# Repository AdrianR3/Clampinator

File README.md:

# The Clampinator

Inspired by the [ODrive Regen Clamp](https://shop.odriverobotics.com/products/odrive-regeneration-clamp), the clampinator is a custom built regeneration clamp targeting 16-60V systems.

## Key Features
 - 16-60V input
 - Adjustable clamp voltage via trimpot
 - Full reverse current protection via TI's [LM7481-Q1](https://www.ti.com/product/LM7481-Q1)
   - Ideal diode inrush current limiting supported, but marked as DNP
 - External pre-charge resistor
 - **FULL galvanic isolation between power and logic domains**
 - USB-C port for programming
 - STM32H5 based logic control
   - Digital control to disconnect power input from output
   - 2x CAN FD exposed w/toggleable termination resistors
 - Two onboard LEDs (Yellow and RGB)
 - Two 10k thermistor slots for thermistors
 - Two 15V outputs for active cooling fans

> [!CAUTION]
> The Clampinator must not be plugged in unless the power switch is off. To turn on, slide power switch to `PRECHARGE`, and only proceed to `RUN` after allowing at least 1s for the bulk capacitors to charge.

## Using the CAN bus

The STM32 on the board is equipped with two built in CAN FD controllers, and the Clampinator has two accompanying CAN transcievers in the bottom left of the board. There is dip switch `SW5` which can be used to toggle the internal 120Ω termination resistors.

## Building the Clampinator
The Clampinator can be ordered from sites like JLCPCB. The KiCAD source files are in `./KiCAD` and the production gerber files are in `./KiCAD/prod` along with the bom.

## Images 

## Schematic

### Main Circuit

## Logic Side Circuit

## Thermal Management

## BOM

| **Name**              | **Purpose**                                     | **Quantity** | **Total Cost (USD)** | **Link**                                                                                                                      | **Distributor**   |
|-----------------------|-------------------------------------------------|--------------|----------------------|-------------------------------------------------------------------------------------------------------------------------------|-------------------|
| LCSC Parts            | Majority of PCB Components (With GSDL selected) |              | 124.28               |                                                                                                                               | LCSC              |
| 150R 25W Resistor     | Precharge Resistor (Inrush Current Limiting)    | 1            | 5.19                 | https://www.digikey.com/en/products/detail/riedon-products-by-bourns/UAL25-150RF8/3886469                                     | DigiKey           |
| 1818-VP036584000AG-ND | Connect Main Power                              | 2            | 5.50                 | https://www.digikey.com/en/products/detail/amphenol-anytek/VP036584000AG/10378245                                             | DigiKey           |
| 1818-VP0265840000G-ND | Connect Precharge Resistor                      | 1            | 3.10                 | https://www.digikey.com/en/products/detail/amphenol-anytek/VP0265840000G/10378270                                             | DigiKey           |
| EG1847-ND             | Switch for Logic Side of Board                  |              | 0.89                 | https://www.digikey.com/en/products/detail/e-switch/EG1270/6076                                                               | DigiKey           |
| 259-1805-ND           | Active Cooling Fan (price includes est. tariff) | 2            | 15.48                | https://www.digikey.com/en/products/detail/sunon-fans/MF80252V1-1000U-A99/6198743                                             | DigiKey           |
| SW115-ND              | (GPI-154-3013) Precharge Switch                 |              | 1.83                 | https://www.digikey.com/en/products/detail/cw-industries/GPI-154-3013/902                                                     | DigiKey           |
| 1.6R 500W Resistor    | Main brake resistor                             |              | 29.99                | https://www.youdaelectronics.com/products/1pc-500w-watt-16-ohm-500w-16r-aluminum-housing-wire-wound-resistor-29x52x250mm-3199 | Youda Electronics |
| JLCPCB + Stencil      | Main Clampinator Board                          | 1            | 101.38               |                                                                                                                               | JLCPCB            |

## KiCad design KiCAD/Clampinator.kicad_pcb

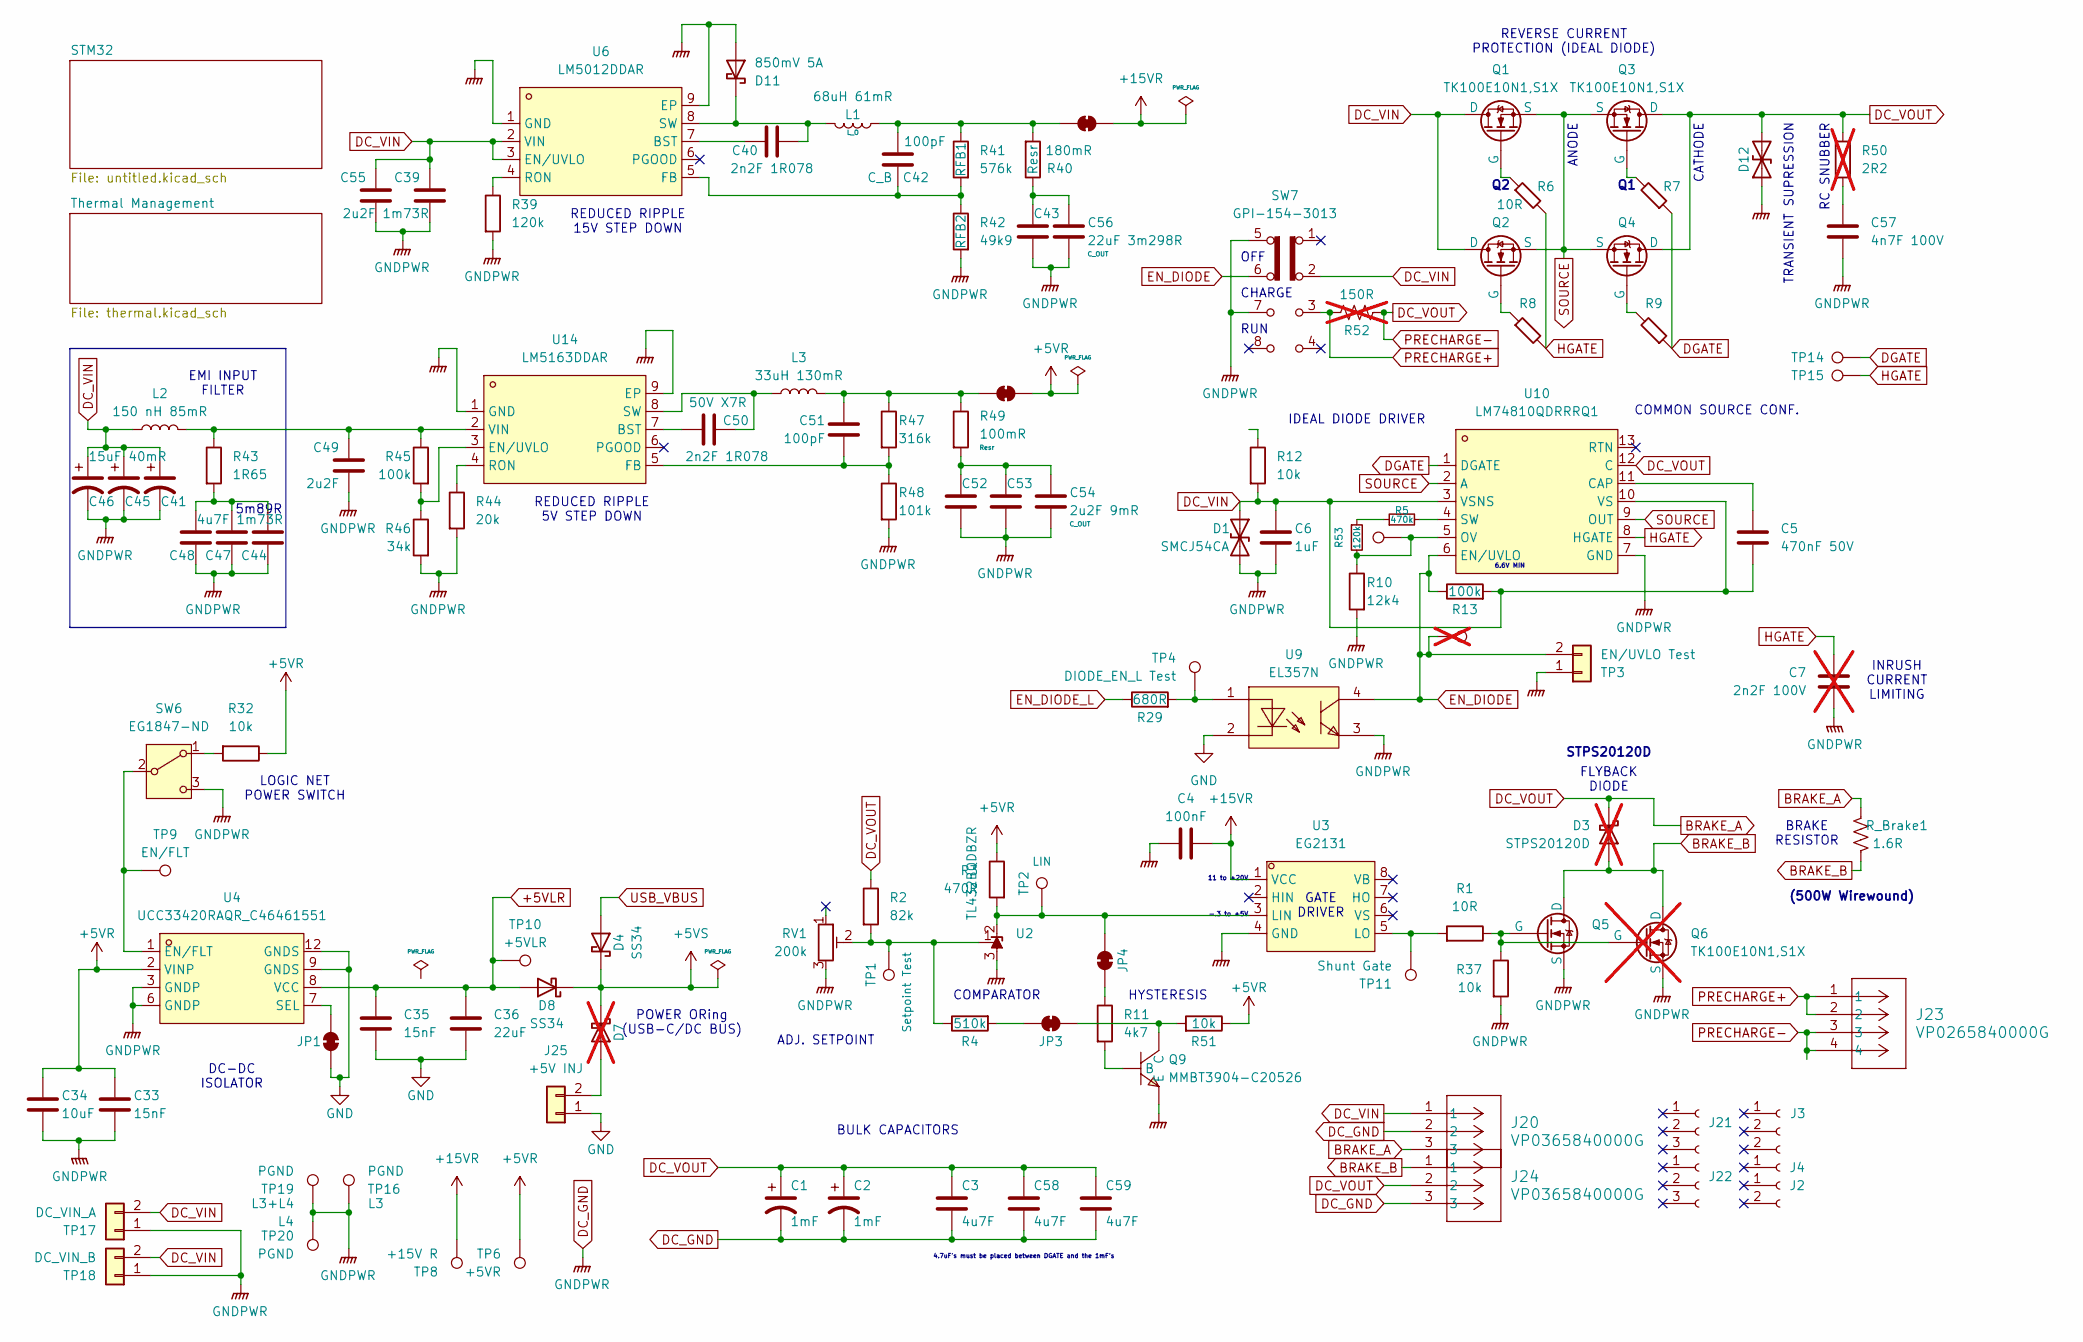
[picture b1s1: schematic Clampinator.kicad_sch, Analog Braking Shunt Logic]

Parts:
C1, C2: 1mF; CP_Radial_D18.0mm_P7.50mm; MPN ECA2AM102; LCSC Part C178408
C3, C58, C59: 4u7F; C_1210_3225Metric; LCSC Part C915836
C4: 100nF; C_0402_1005Metric; LCSC Part C307331
C5: 470nF 50V; C_0603_1608Metric; LCSC Part C1620
C6: 1uF; C_1206_3216Metric; LCSC Part C13832
C7: 2n2F 100V; C_0603_1608Metric; not fitted
C33, C35: 15nF; C_0402_1005Metric; LCSC Part C1548
C34: 10uF; C_0805_2012Metric; LCSC Part C15850
C36: 22uF; C_1206_3216Metric; LCSC Part C12891
C39, C55: 2u2F 1m73R; C_1206_3216Metric; LCSC Part C5122251
C40, C50: 2n2F 1R078; C_0603_1608Metric; LCSC Part C1604
C41, C45, C46: 15uF 40mR; CAP-SMD_BD8.0-L8.3-W8.3-LS9.3-FD; MPN 100SXV15M; LCSC Part C542593
C42, C51: 100pF; C_0402_1005Metric; LCSC Part C1546
C43, C56: 22uF 3m298R; C_1206_3216Metric; LCSC Part C12891
C44, C47, C48: 4u7F 1m73R; C_1210_3225Metric; LCSC Part C915836
C49: 2u2F; C_1206_3216Metric; LCSC Part C5122251
C52, C53, C54: 2u2F 9mR; C_1206_3216Metric; LCSC Part C5122251
C57: 4n7F 100V; C_1206_3216Metric; LCSC Part C393168
D1: SMCJ54CA; SMC_L6.9-W5.9-LS7.9-BI; MPN SMCJ54CA-13-F; LCSC Part C135179
D3: STPS20120D; TO-220AC_L10.0-W4.5-P5.08-T; MPN STPS20120D; LCSC Part C10623; not fitted
D4, D8: SS34; D_SMA; LCSC Part C8678
D7: SS34; D_SMA; LCSC Part C8678; not fitted
D11: 850mV 5A; D_SMA; LCSC Part C65010
D12: SMCJ64CA; SMC_L6.9-W5.9-LS7.9-BI; MPN SMCJ64CA/TR13; LCSC Part C123977
J2, J3, J4: Conn_01x02_Socket; PinHeader_1x02_P2.54mm_Vertical
J20, J24: VP0365840000G; VP0265840000G_THT; DigiKey BOM YES
J21, J22: Conn_01x03_Socket
J23: VP0265840000G; CONN04_VP026584_20P32X18P3_AMP; DigiKey BOM YES
J25: +5V INJ; PinHeader_1x02_P2.54mm_Vertical
JP1: SolderJumper_2_Bridged; SolderJumper-2_P1.3mm_Bridged2Bar_RoundedPad1.0x1.5mm
JP3, JP4: SolderJumper_2_Bridged; SolderJumper-2_P1.3mm_Bridged_RoundedPad1.0x1.5mm
JP5: SolderJumper_2_Bridged; SolderJumper-2_P1.3mm_Bridged2Bar_Pad1.0x1.5mm
JP6: +15VR; SolderJumper-2_P1.3mm_Bridged2Bar_Pad1.0x1.5mm
L1: 68uH 61mR; IND-SMD_L12.5-W12.5; MPN CYH125-68UH; LCSC Part C7431083
L2: 150 nH 85mR; WE-MAPI_2010; MPN 744383430033; LCSC Part C6069597
L3: 33uH 130mR; IND_SRR6038-330Y; MPN SRR6038-330Y; LCSC Part C2041395
Q1, Q2, Q3, Q4, Q5: TK100E10N1,S1X; TO-220-3_L10.0-W4.5-P2.54-L; MPN TK100E10N1,S1X; LCSC Part C5986394
Q6: TK100E10N1,S1X; TO-220-3_L10.0-W4.5-P2.54-L; MPN TK100E10N1,S1X; LCSC Part C5986394; not fitted
Q9: MMBT3904-C20526; SOT-23-3_L2.9-W1.3-P1.90-LS2.4-BR; MPN MMBT3904(RANGE:100-300); LCSC Part C20526
R1, R6, R7, R8, R9: 10R; R_0805_2012Metric; LCSC Part C17415
R2: 82k; R_0805_2012Metric; LCSC Part C2849357
R3: 470R; R_0603_1608Metric; LCSC Part C23179
R4: 510k; R_0603_1608Metric; LCSC Part C23192
R5: 470k; R_0805_2012Metric; LCSC Part C17709
R10: 12k4; R_0402_1005Metric; LCSC Part C25752
R11: 4k7; R_0402_1005Metric; LCSC Part C25900
R12: 10k; R_1206_3216Metric; LCSC Part C17902
R13, R45: 100k; R_1206_3216Metric; LCSC Part C17900
R29: 680R; R_0603_1608Metric; LCSC Part C23228
R32, R51: 10k; R_0402_1005Metric; LCSC Part C25744
R37: 10k; R_0805_2012Metric; LCSC Part C17414
R39, R53: 120k; R_0603_1608Metric; LCSC Part C25808
R40: 180mR; R_1206_3216Metric; LCSC Part C24436
R41: 576k; R_0603_1608Metric; LCSC Part C245981
R42: 49k9; R_0603_1608Metric; LCSC Part C23184
R43: 1R65; R_1206_3216Metric; LCSC Part C79297
R44: 20k; R_0603_1608Metric; LCSC Part C4184
R46: 34k; R_0805_2012Metric; LCSC Part C2077219
R47: 316k; R_0603_1608Metric; LCSC Part C185340
R48: 101k; R_0805_2012Metric; LCSC Part C7302896
R49: 100mR; R_1206_3216Metric; LCSC Part C25334
R50: 2R2; R_1210_3225Metric; MPN ERJ-P08J2R2V; not fitted
R52: 150R; SolderWire-4sqmm_1x02_P12mm_D3mm_OD6mm; MPN UAL25-150RF8; DigiKey BOM YES; not fitted
RV1: 200k; RES-ADJ-TH_3P-L9.5-W4.9-P2.50-L_3296W; MPN 3296W-1-204LF; LCSC Part C49190460
R_Brake1: 1.6R
SW6: EG1847-ND; SW_EG1270; DigiKey BOM YES
SW7: GPI-154-3013; SW_Slide_GPL-154-3013_DP3T_Angled; DigiKey BOM YES
TP1: Setpoint Test; TestPoint_THTPad_D2.0mm_Drill1.0mm
TP2: LIN; PinHeader_1x01_P2.54mm_Vertical
TP3: EN/UVLO Test; PinHeader_1x02_P2.54mm_Vertical
TP4: DIODE_EN_L Test; TestPoint_THTPad_D2.0mm_Drill1.0mm
TP6: +5VR; TestPoint_THTPad_D2.0mm_Drill1.0mm
TP8: +15V R; TestPoint_THTPad_D2.0mm_Drill1.0mm
TP9: EN/FLT; TestPoint_THTPad_D1.0mm_Drill0.5mm
TP10: +5VLR; TestPoint_THTPad_D1.0mm_Drill0.5mm
TP11: Shunt Gate; PinHeader_1x01_P2.54mm_Vertical
TP13: TestPoint; TestPoint_THTPad_D1.5mm_Drill0.7mm
TP14: D; TestPoint_THTPad_D1.0mm_Drill0.5mm
TP15: H; TestPoint_THTPad_D1.0mm_Drill0.5mm
TP16, TP19, TP20: PGND; TestPoint_THTPad_D2.0mm_Drill1.0mm
TP17: DC_VIN_A; PinHeader_1x02_P2.54mm_Vertical
TP18: DC_VIN_B; PinHeader_1x02_P2.54mm_Vertical
TP-not3: EN/UVLO Test; TestPoint_THTPad_D2.0mm_Drill1.0mm; not fitted
U2: TL432BQDBZR; SOT-23; LCSC Part C53724
U3: EG2131; SOIC-8_L5.0-W4.0-P1.27-LS6.0-BL; MPN EG2131; LCSC Part C193777
U4: UCC33420RAQR_C46461551; VSON-12_L5.0-W4.0-P0.65-TL_PUCC33420QRAQRQ1; MPN UCC33420RAQR; LCSC Part C46461551
U6: LM5012DDAR; SOPOWERPAD-8_L4.9-W3.9-P1.27-LS6.0-BL-EP; MPN LM5012DDAR; LCSC Part C6079494
U9: EL357N; OPTO-SMD-4_L4.4-W4.1-P2.54-LS7.0-TL; MPN EL357N(A)(TA)-G; LCSC Part C42385000
U10: LM74810QDRRRQ1; WSON-12_L3.0-W3.0-P0.50-TL-EP-2; MPN LM74810QDRRRQ1; LCSC Part C3215601
U14: LM5163DDAR; ESOP-8_L4.9-W3.9-P1.27-LS6.0-BL-EP2.6; MPN LM5163DDAR; LCSC Part C2873264

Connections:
+5VLR: C35.1, C36.1, D8.2 (A), TP10.1 (1_1), U4.8 (VCC)
+5VR: C33.1, C34.1, JP5.2 (B), R3.1, R32.1, R51.1, TP6.1 (1_1), U4.2 (VINP); also elsewhere on the board
+5VS: D4.1 (K), D7.1 (K), D8.1 (K); also elsewhere on the board
+15VR: C4.2, JP6.2 (B), TP8.1 (1_1), U3.1 (VCC); also elsewhere on the board
BRAKE_A: C1.1, C2.1, C3.1, C58.1, C59.1, D3.1 (K), D12.2 (A2), J20.3, J23.3, J23.4, J24.2, Q3.1 (D), Q4.1 (D), R2.1, R50.1, R52.2, R_Brake1.2, U10.12 (C)
BRAKE_B: D3.2 (A), J24.1, Q5.1 (D), Q6.1 (D), R_Brake1.1
DC_GND: C1.2, C2.2, C3.2, C4.1, C6.2, C7.2, C33.2, C34.2, C39.2, C41.2, C43.2, C44.2, C45.2, C46.2, C47.2, C48.2, C49.2, C52.2, C53.2, C54.2, C55.2, C56.2, C57.2, C58.2, C59.2, D1.2 (A2), D11.2 (A), D12.1 (A1), J20.2, J24.3, Q5.3 (S), Q6.3 (S), Q9.2 (E), R10.2, R37.2, R39.2, R42.2, R44.2, R46.2, R48.2, RV1.3, SW6.3 (C), SW7.5 (B), SW7.7 (C), TP3.1, TP16.1 (1_1), TP17.1, TP18.1, TP19.1 (1_1), TP20.1 (1_1), U2.3 (A), U3.4 (GND), U4.3 (GNDP), U4.6 (GNDP), U6.1 (GND), U6.9 (EP), U9.3 (EM), U10.7 (GND), U14.1 (GND), U14.9 (EP); also elsewhere on the board
DC_VIN: C5.2, C6.1, C39.1, C41.1, C45.1, C46.1, C55.1, D1.1 (A1), J20.1, L2.1, Q1.1 (D), Q2.1 (D), R12.2, R13.2, SW7.2 (B), TP17.2, TP18.2, U6.2 (VIN), U6.3 (EN/UVLO), U10.3 (VSNS), U10.10 (VS)
DGATE: R7.1, R9.1, TP14.1 (1_1), U10.1 (DGATE)
EN_DIODE: R13.1, SW7.6 (C), TP3.2, TP-not3.1, U9.4 (COL), U10.6 (EN/UVLO)
EN_DIODE_L: R29.1; also elsewhere on the board
GND: C35.2, C36.2, J25.1, JP1.1 (A), U4.9 (GNDS), U4.12 (GNDS), U9.2 (CA); also elsewhere on the board
HGATE: C7.1, R6.2, R8.2, TP15.1 (1_1), U10.8 (HGATE)
unnamed: C43.1, C56.1, R40.1
unnamed: C44.1, C47.1, C48.1, R43.2
unnamed: C52.1, C53.1, C54.1, R49.2
unnamed: C57.1, R50.2
unnamed: D7.2 (A), J25.2
unnamed: C40.2, D11.1 (K), L1.2, U6.8 (SW)
unnamed: JP1.2 (B), U4.7 (SEL)
unnamed: JP3.1 (A), R4.2
unnamed: JP3.2 (B), Q9.3 (C), R51.2
unnamed: JP4.1 (A), R3.2, TP2.1 (1_1), U2.2 (K), U3.3 (LIN)
unnamed: JP4.2 (B), R11.1
unnamed: C51.1, JP5.1 (A), L3.2, R47.1, R49.1
unnamed: C42.1, JP6.1 (A), L1.1, R40.2, R41.1
unnamed: Q1.2 (G), R6.1
unnamed: Q2.2 (G), R8.1
unnamed: Q3.2 (G), R7.2
unnamed: Q4.2 (G), R9.2
unnamed: Q5.2 (G), Q6.2 (G), R1.1, R37.1
unnamed: Q9.1 (B), R11.2
unnamed: R5.1, R53.1
unnamed: R32.2, SW6.1 (A)
unnamed: SW6.2 (B), TP9.1 (1_1), U4.1 (EN/FLT)
unnamed: R2.2, R4.1, RV1.2, TP1.1 (1_1), U2.1 (REF)
unnamed: R1.2, TP11.1 (1_1), U3.5 (LO)
unnamed: C40.1, U6.7 (BST)
unnamed: C42.2, R41.2, R42.1, U6.5 (FB)
unnamed: R39.1, U6.4 (RON)
unnamed: R29.2, TP4.1 (1_1), U9.1 (AN)
unnamed: C5.1, U10.11 (CAP)
unnamed: R10.1, R53.2, TP13.1 (1_1), U10.5 (OV)
unnamed: R5.2, U10.4 (SW)
unnamed: C50.2, U14.7 (BST)
unnamed: R45.2, R46.1, U14.3 (EN/UVLO)
unnamed: C51.2, R47.2, R48.1, U14.5 (FB)
unnamed: R44.1, U14.4 (RON)
unnamed: C50.1, L3.1, U14.8 (SW)
unnamed: C49.1, L2.2, R43.1, R45.1, U14.2 (VIN)
PRECHARGE+: J23.1, J23.2, R52.1, SW7.3 (C)
SOURCE: Q1.3 (S), Q2.3 (S), Q3.3 (S), Q4.3 (S), U10.2 (A), U10.9 (OUT)
USB_VBUS: D4.2 (A); also elsewhere on the board

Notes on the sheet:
ANODE
RC SNUBBER
HYSTERESIS
4.7uF's must be placed between DGATE and the 1mF's
COMMON SOURCE CONF.
GATE DRIVER
REVERSE CURRENT PROTECTION (IDEAL DIODE)
IDEAL DIODE DRIVER
DC-DC ISOLATOR
STPS20120D
FLYBACK DIODE
11 to +20V
CATHODE
CHARGE
6.6V MIN
EMI INPUT FILTER
RUN
LOGIC NET POWER SWITCH
-.3 to +5V
REDUCED RIPPLE 15V STEP DOWN
OFF
REDUCED RIPPLE 5V STEP DOWN
BULK CAPACITORS
(500W Wirewound)
BRAKE RESISTOR
COMPARATOR
INRUSH CURRENT LIMITING
TRANSIENT SUPRESSION
5m89R
ADJ. SETPOINT
POWER ORing (USB-C/DC BUS)

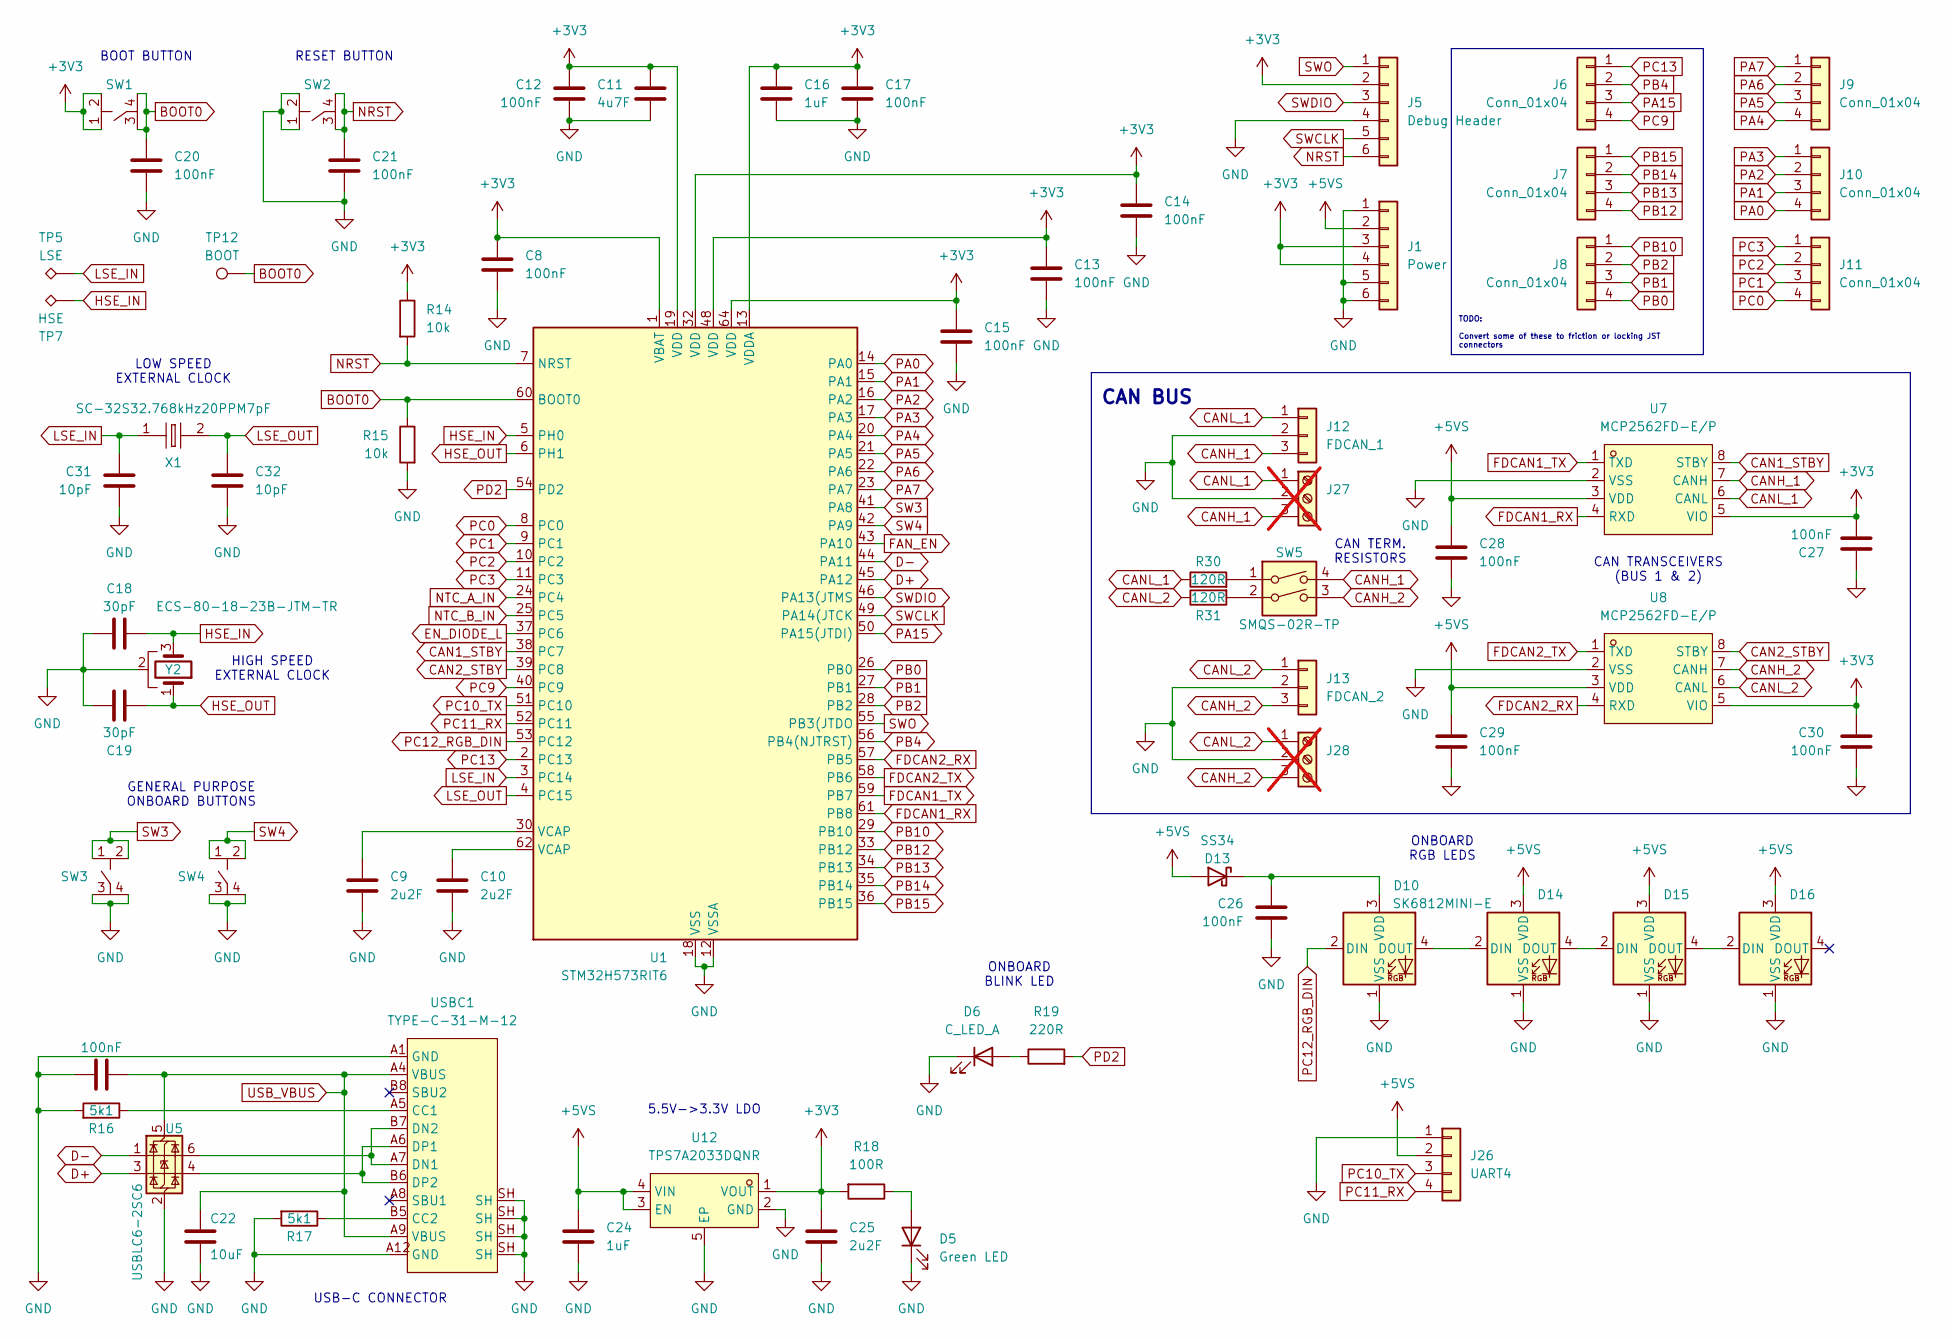
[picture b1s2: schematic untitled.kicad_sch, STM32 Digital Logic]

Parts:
C8, C12, C13, C14, C15, C17, C26, C27, C30: 100nF; C_0402_1005Metric; LCSC Part C1525
C9, C10, C25: 2u2F; C_0603_1608Metric; LCSC Part C23630
C11: 4u7F; C_0603_1608Metric; LCSC Part C19666
C16: 1uF; C_0603_1608Metric; LCSC Part C15849
C18, C19: 30pF; C_0603_1608Metric; LCSC Part C1658
C20, C21: 100nF; C_0603_1608Metric; LCSC Part C14663
C22: 10uF; C_0805_2012Metric; LCSC Part C440198
C23, C28, C29: 100nF; C_0402_1005Metric; LCSC Part C307331
C24: 1uF; C_0402_1005Metric; LCSC Part C52923
C31, C32: 10pF; C_0402_1005Metric; LCSC Part C32949
D5: Green LED; LED_0805_2012Metric; LCSC Part C2297
D6: C_LED_A; LED_0805_2012Metric; LCSC Part C2296
D10, D14, D15, D16: SK6812MINI-E; LED_SK6812MINI-E_3.2x2.8mm_P1.5mm
D13: SS34; D_SMA; LCSC Part C8678
J1: Power; PinHeader_1x06_P2.54mm_Vertical
J5: Debug Header; PinHeader_1x06_P2.54mm_Vertical
J6, J7, J8, J9, J10, J11: Conn_01x04; PinHeader_1x04_P2.54mm_Vertical
J12: FDCAN_1; PinHeader_1x03_P2.54mm_Vertical
J13: FDCAN_2; PinHeader_1x03_P2.54mm_Vertical
J26: UART4; PinHeader_1x04_P2.54mm_Vertical
J27, J28: Screw_Terminal_01x03; CONN-TH_3P-P3.50_OSTTE030161; not fitted
R14, R15: 10k; R_0402_1005Metric; LCSC Part C25744
R16, R17: 5k1; R_0402_1005Metric; LCSC Part C25905
R18: 100R; R_0603_1608Metric; LCSC Part C22775
R19: 220R; R_0603_1608Metric; LCSC Part C22962
R30, R31: 120R; R_1206_3216Metric; LCSC Part C17909
SW1, SW2, SW3, SW4: PTS810SJM250SMTRLFS; KEY-SMD_4P-L4.2-W3.2-P2.20-LS4.6; MPN PTS810SJM250SMTRLFS; LCSC Part C116501
SW5: SMQS-02R-TP; SW-TH_4P-L9.9-W6.8-P7.62-BL; MPN SMQS-02R-TP; LCSC Part C5299503
TP5: LSE; TestPoint_Pad_2.0x2.0mm
TP7: HSE; TestPoint_Pad_2.0x2.0mm
TP12: BOOT; TestPoint_THTPad_D1.5mm_Drill0.7mm
U1: STM32H573RIT6; LQFP-64_10x10mm_P0.5mm; LCSC Part C22371377
U5: USBLC6-2SC6; SOT-23-6; LCSC Part C7519
U7, U8: MCP2562FD-E/P; PDIP-8_L9.3-W6.4-P2.54-LS7.6-BL; MPN MCP2562FD-E/P; LCSC Part C640346
U12: TPS7A2033DQNR; UDFN-4_L1.0-W1.0-P0.65-TL; MPN TPS7A2033DQNR; LCSC Part C46459900
USBC1: TYPE-C-31-M-12; USB_C_Receptacle_HRO_TYPE-C-31-M-12; MPN TYPE-C-31-M-12; LCSC Part C165948
X1: SC-32S32.768kHz20PPM7pF; OSC-SMD_L3.2-W1.5; MPN SC-32S32.768kHz20PPM7pF; LCSC Part C97604
Y2: ECS-80-18-23B-JTM-TR; CRYSTAL-SMD_4P-L6.0-W3.5-BL; MPN ECS-80-18-23B-JTM-TR; LCSC Part C2450633

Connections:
+3V3: C8.1, C11.1, C12.1, C13.1, C14.1, C15.1, C16.1, C17.1, C25.1, C27.1, C30.1, J1.3, J1.4, J5.2, R14.1, R18.2, SW1.1, SW1.2, U1.1 (VBAT), U1.13 (VDDA), U1.19 (VDD), U1.32 (VDD), U1.48 (VDD), U1.64 (VDD), U7.5 (VIO), U8.5 (VIO), U12.1 (VOUT); also elsewhere on the board
+5VS: C24.1, C28.1, C29.2, D13.2 (A), D14.3 (VDD), D15.3 (VDD), D16.3 (VDD), J1.2, J26.2, U7.3 (VDD), U8.3 (VDD), U12.3 (EN), U12.4 (VIN); also elsewhere on the board
BOOT0: C20.1, R15.1, SW1.3, SW1.4, TP12.1 (1_1), U1.60 (BOOT0)
CAN1_STBY: U1.38 (PC7), U7.8 (STBY)
CAN2_STBY: U1.39 (PC8), U8.8 (STBY)
CANH_1: J12.3, J27.3, SW5.4, U7.7 (CANH)
CANH_2: J13.3, J28.3, SW5.3, U8.7 (CANH)
CANL_1: J12.1, J27.1, R30.1, U7.6 (CANL)
CANL_2: J13.1, J28.1, R31.1, U8.6 (CANL)
D+: U1.45 (PA12), U5.3 (I/O2)
D-: U1.44 (PA11), U5.1 (I/O1)
EN_DIODE_L: U1.37 (PC6); also elsewhere on the board
FAN_EN: U1.43 (PA10); also elsewhere on the board
FDCAN1_RX: U1.61 (PB8), U7.4 (RXD)
FDCAN1_TX: U1.59 (PB7), U7.1 (TXD)
FDCAN2_RX: U1.57 (PB5), U8.4 (RXD)
FDCAN2_TX: U1.58 (PB6), U8.1 (TXD)
GND: C8.2, C9.2, C10.2, C11.2, C12.2, C13.2, C14.2, C15.2, C16.2, C17.2, C18.1, C19.2, C20.2, C21.2, C22.2, C23.2, C24.2, C25.2, C26.2, C27.2, C28.2, C29.1, C30.2, C31.2, C32.2, D5.1 (K), D6.1 (K), D10.1 (VSS), D14.1 (VSS), D15.1 (VSS), D16.1 (VSS), J1.1, J1.5, J1.6, J5.4, J12.2, J13.2, J26.1, J27.2, J28.2, R15.2, R16.2, R17.2, SW2.1, SW2.2, SW3.3, SW3.4, SW4.3, SW4.4, U1.12 (VSSA), U1.18 (VSS), U1.31 (VSS), U1.47 (VSS), U1.63 (VSS), U5.2 (GND), U7.2 (VSS), U8.2 (VSS), U12.2 (GND), U12.5 (EP), USBC1.A1 (GND), USBC1.A12 (GND), USBC1.B1 (GND), USBC1.B12 (GND), USBC1.SH, Y2.2, Y2.4; also elsewhere on the board
HSE_IN: C18.2, TP7.1 (1_1), U1.5 (PH0), Y2.3
HSE_OUT: C19.1, U1.6 (PH1), Y2.1
LSE_IN: C31.1, TP5.1 (1_1), U1.3 (PC14), X1.1
LSE_OUT: C32.1, U1.4 (PC15), X1.2
NRST: C21.1, J5.6, R14.2, SW2.3, SW2.4, U1.7 (NRST)
NTC_A_IN: U1.24 (PC4); also elsewhere on the board
NTC_B_IN: U1.25 (PC5); also elsewhere on the board
unnamed: C9.1, U1.30 (VCAP)
unnamed: C10.1, U1.62 (VCAP)
unnamed: D5.2 (A), R18.1
unnamed: D6.2 (A), R19.1
unnamed: D10.4 (DOUT), D14.2 (DIN)
unnamed: C26.1, D10.3 (VDD), D13.1 (K)
unnamed: D14.4 (DOUT), D15.2 (DIN)
unnamed: D15.4 (DOUT), D16.2 (DIN)
unnamed: R30.2, SW5.1
unnamed: R31.2, SW5.2
unnamed: R16.1, USBC1.A5 (CC1)
unnamed: R17.1, USBC1.B5 (CC2)
unnamed: U5.6 (I/O1), USBC1.A7 (DN1), USBC1.B7 (DN2)
unnamed: U5.4 (I/O2), USBC1.A6 (DP1), USBC1.B6 (DP2)
PA0: J10.4, U1.14 (PA0)
PA1: J10.3, U1.15 (PA1)
PA2: J10.2, U1.16 (PA2)
PA3: J10.1, U1.17 (PA3)
PA4: J9.4, U1.20 (PA4)
PA5: J9.3, U1.21 (PA5)
PA6: J9.2, U1.22 (PA6)
PA7: J9.1, U1.23 (PA7)
PA15: J6.3, U1.50 (PA15(JTDI))
PB0: J8.4, U1.26 (PB0)
PB1: J8.3, U1.27 (PB1)
PB2: J8.2, U1.28 (PB2)
PB4: J6.2, U1.56 (PB4(NJTRST))
PB10: J8.1, U1.29 (PB10)
PB12: J7.4, U1.33 (PB12)
PB13: J7.3, U1.34 (PB13)
PB14: J7.2, U1.35 (PB14)
PB15: J7.1, U1.36 (PB15)
PC0: J11.4, U1.8 (PC0)
PC1: J11.3, U1.9 (PC1)
PC2: J11.2, U1.10 (PC2)
PC3: J11.1, U1.11 (PC3)
PC9: J6.4, U1.40 (PC9)
PC10_TX: J26.3, U1.51 (PC10)
PC11_RX: J26.4, U1.52 (PC11)
PC12_RGB_DIN: D10.2 (DIN), U1.53 (PC12)
PC13: J6.1, U1.2 (PC13)
PD2: R19.2, U1.54 (PD2)
SW3: SW3.1, SW3.2, U1.41 (PA8)
SW4: SW4.1, SW4.2, U1.42 (PA9)
SWCLK: J5.5, U1.49 (PA14(JTCK)
SWDIO: J5.3, U1.46 (PA13(JTMS)
SWO: J5.1, U1.55 (PB3(JTDO)
USB_VBUS: C22.1, C23.1, U5.5 (VBUS), USBC1.A4 (VBUS), USBC1.A9 (VBUS), USBC1.B4 (VBUS), USBC1.B9 (VBUS); also elsewhere on the board

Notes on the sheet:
CAN BUS
ONBOARD RGB LEDS
USB-C CONNECTOR
LOW SPEED EXTERNAL CLOCK
CAN TRANSCEIVERS (BUS 1 & 2)
HIGH SPEED EXTERNAL CLOCK
BOOT BUTTON
ONBOARD BLINK LED
CAN TERM. RESISTORS
RESET BUTTON
5.5V->3.3V LDO
GENERAL PURPOSE ONBOARD BUTTONS
TODO: Convert some of these to friction or locking JST connectors

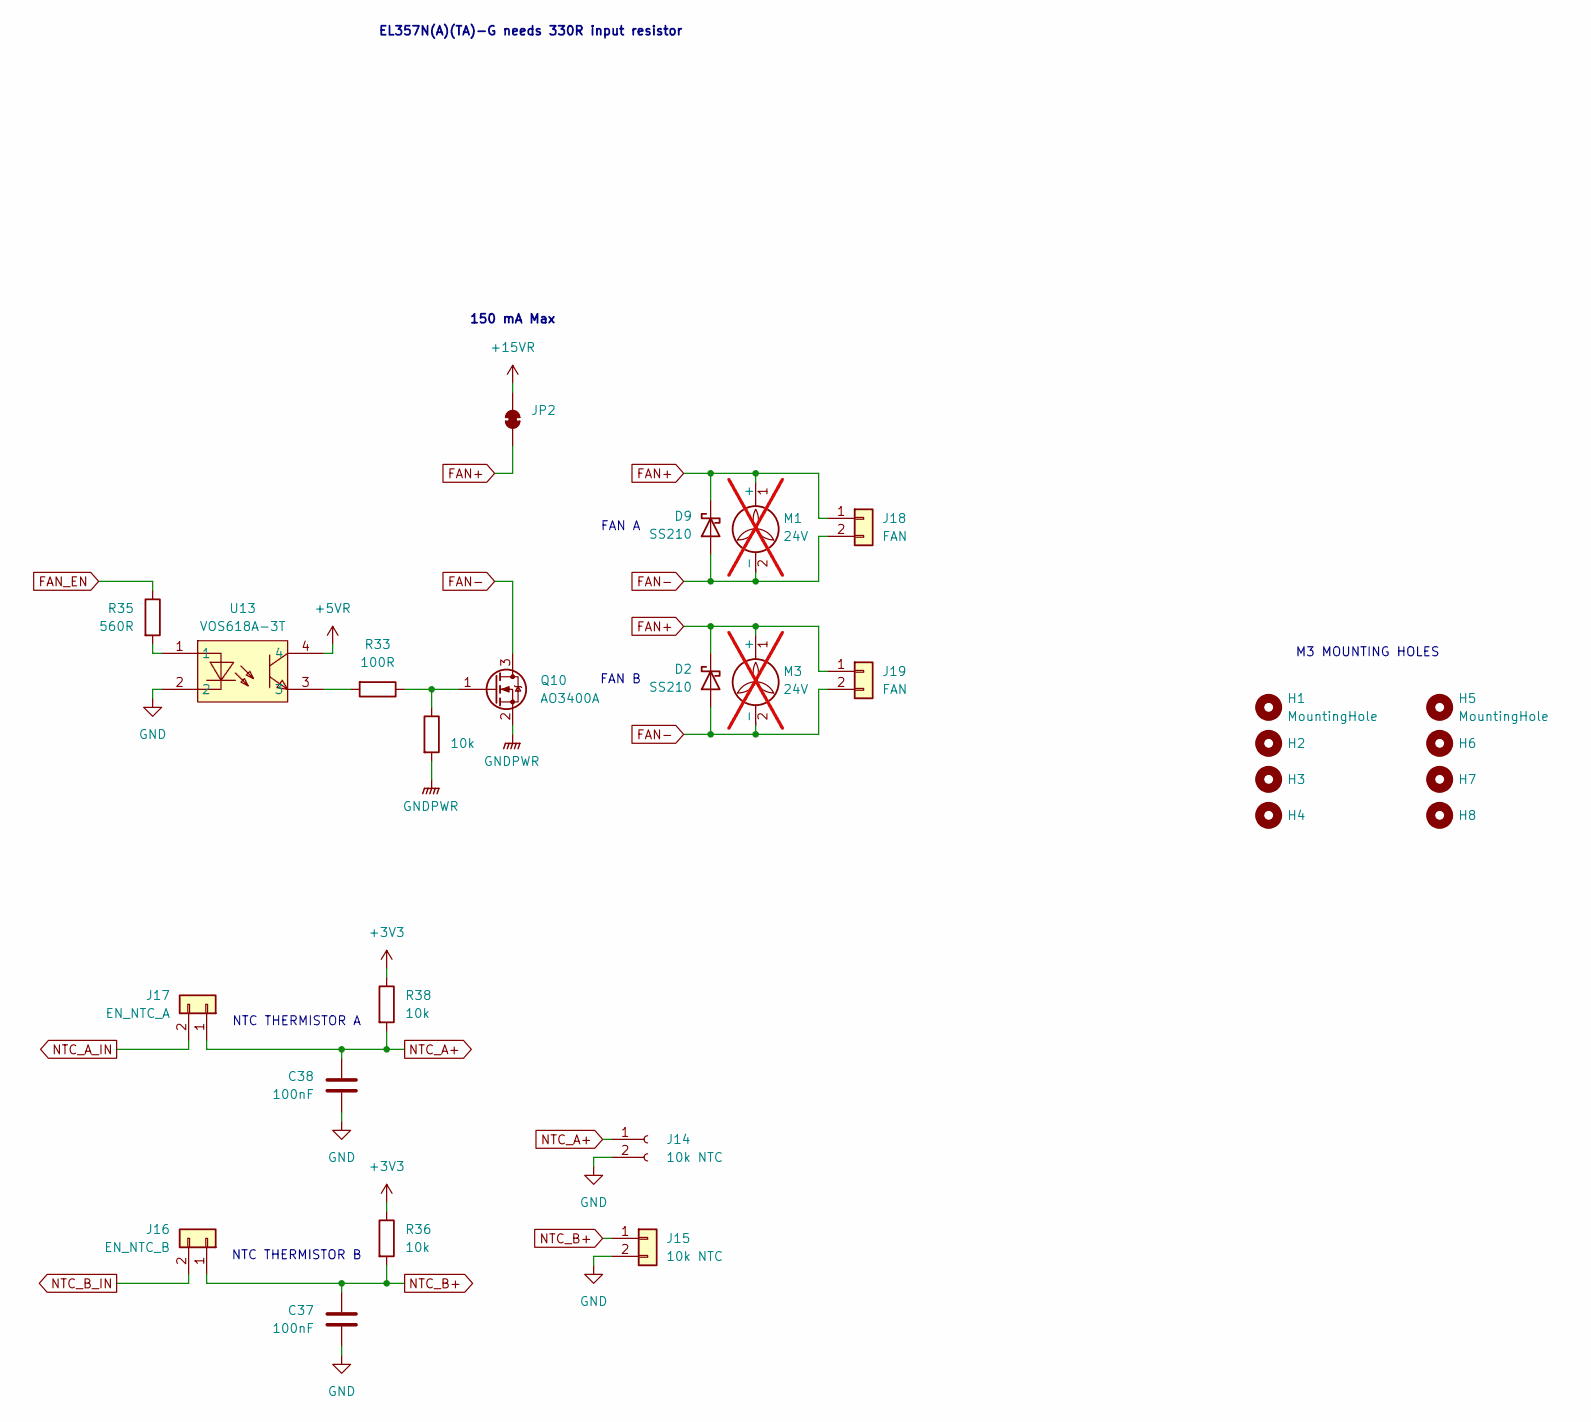
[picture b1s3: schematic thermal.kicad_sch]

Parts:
C37, C38: 100nF; C_0603_1608Metric; LCSC Part C14663
D2, D9: SS210; D_SMA; LCSC Part C14996
H1, H2, H3, H4, H5, H6, H7, H8: MountingHole; MountingHole_3.2mm_M3
J14: 10k NTC; JST_PH_B2B-PH-K_1x02_P2.00mm_Vertical
J15: 10k NTC; PinHeader_1x02_P2.54mm_Vertical
J16: EN_NTC_B; PinHeader_1x02_P2.54mm_Vertical
J17: EN_NTC_A; PinHeader_1x02_P2.54mm_Vertical
J18, J19: FAN; PinHeader_1x02_P2.54mm_Vertical
JP2: SolderJumper_2_Bridged; SolderJumper-2_P1.3mm_Bridged2Bar_Pad1.0x1.5mm
M1, M3: 24V; MPN MF80252V1-1000U-A99; DigiKey BOM YES; not fitted
Q10: AO3400A; SOT-23; LCSC Part C20917
R33: 100R; R_0402_1005Metric; LCSC Part C25076
R34, R36, R38: 10k; R_0402_1005Metric; LCSC Part C25744
R35: 560R; R_0603_1608Metric; LCSC Part C23204
U13: VOS618A-3T; SOP-4_L4.4-W2.6-P1.27-LS7.0-BL; MPN VOS618A-3T; LCSC Part C17494890

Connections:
+3V3: R36.1, R38.1; also elsewhere on the board
+5VR: U13.4; also elsewhere on the board
+15VR: JP2.2 (B); also elsewhere on the board
DC_GND: Q10.2 (S), R34.2; also elsewhere on the board
FAN+: D2.1 (K), D9.1 (K), J18.1, J19.1, JP2.1 (A), M1.1 (+), M3.1 (+)
FAN-: D2.2 (A), D9.2 (A), J18.2, J19.2, M1.2 (-), M3.2 (-), Q10.3 (D)
FAN_EN: R35.1; also elsewhere on the board
GND: C37.2, C38.2, J14.2, J15.2, U13.2; also elsewhere on the board
NTC_A+: C38.1, J14.1, J17.1, R38.2
NTC_A_IN: J17.2; also elsewhere on the board
NTC_B+: C37.1, J15.1, J16.1, R36.2
NTC_B_IN: J16.2; also elsewhere on the board
unnamed: Q10.1 (G), R33.1, R34.1
unnamed: R33.2, U13.3
unnamed: R35.2, U13.1

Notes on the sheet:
150 mA Max
M3 MOUNTING HOLES
FAN A
NTC THERMISTOR B
NTC THERMISTOR A
FAN B
EL357N(A)(TA)-G needs 330R input resistor

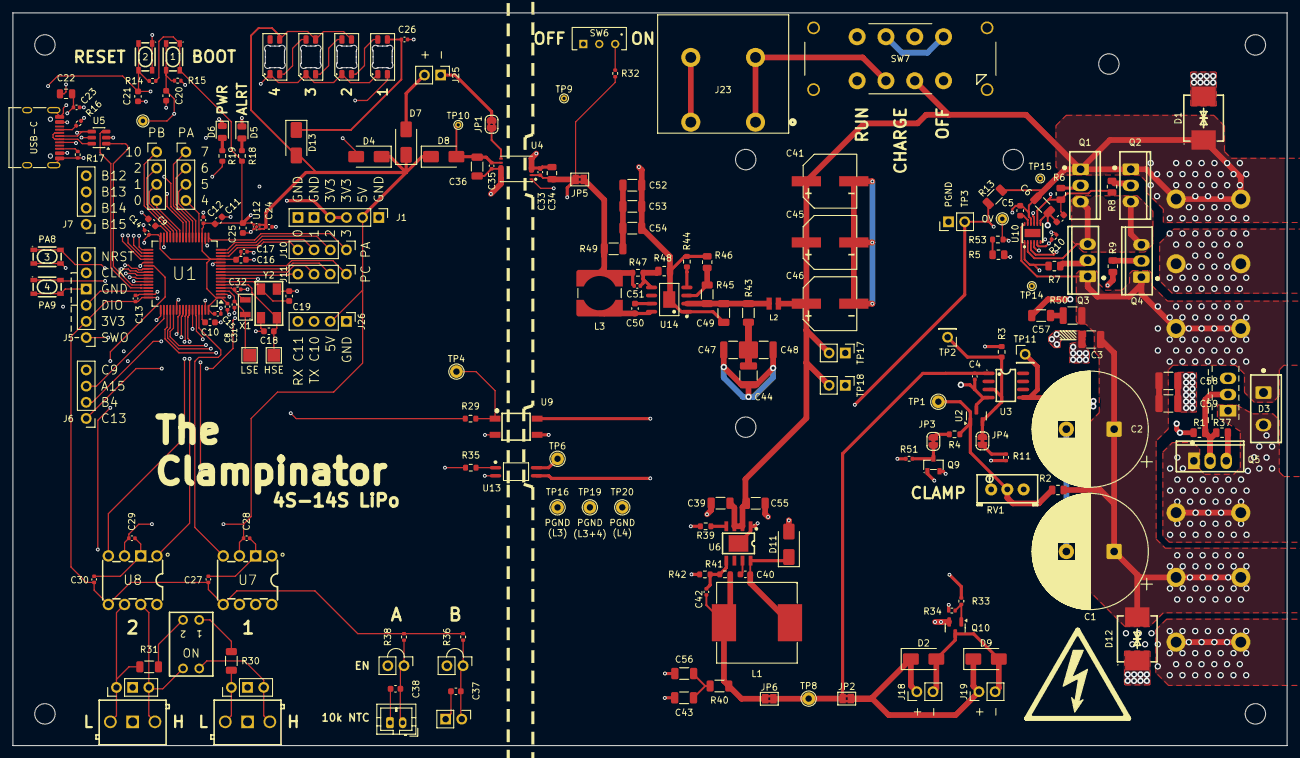
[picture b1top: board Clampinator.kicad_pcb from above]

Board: 4 copper layers, 200.0 x 115.0 mm, 209 parts (0 on the bottom side), 129 nets.

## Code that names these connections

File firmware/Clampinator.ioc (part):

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Mcu.Name=STM32H573RITx
Mcu.Package=LQFP64
Mcu.UserName=STM32H573RITx
PA11.Mode=Device
PA11.Signal=USB_DM
PA12.Mode=Device
PA12.Signal=USB_DP
PA13(JTMS/SWDIO).Mode=Serial_Wire
PA13(JTMS/SWDIO).Signal=DEBUG_JTMS-SWDIO
PA14(JTCK/SWCLK).Mode=Serial_Wire
PA14(JTCK/SWCLK).Signal=DEBUG_JTCK-SWCLK
PB5.Mode=FDCAN_Activate
PB5.Signal=FDCAN2_RX
PB6.Mode=FDCAN_Activate
PB6.Signal=FDCAN2_TX
PB7.Mode=FDCAN_Activate
PB7.Signal=FDCAN1_TX
PB8.Mode=FDCAN_Activate
PB8.Signal=FDCAN1_RX
PC14-OSC32_IN(OSC32_IN).Mode=LSE-External-Oscillator
PC14-OSC32_IN(OSC32_IN).Signal=RCC_OSC32_IN
PC15-OSC32_OUT(OSC32_OUT).Mode=LSE-External-Oscillator
PC15-OSC32_OUT(OSC32_OUT).Signal=RCC_OSC32_OUT
PC4.Signal=ADCx_INP4
PC5.Signal=ADCx_INP8
PH0-OSC_IN(PH0).Mode=HSE-External-Oscillator
PH0-OSC_IN(PH0).Signal=RCC_OSC_IN
PH1-OSC_OUT(PH1).Mode=HSE-External-Oscillator
PH1-OSC_OUT(PH1).Signal=RCC_OSC_OUT
RCC.HSE_VALUE=8000000
RCC.SYSCLKFreq_VALUE=100000000
RCC.SYSCLKSource=RCC_SYSCLKSOURCE_PLLCLK
board=custom

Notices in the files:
parts and their libraries:
slide switch, GPL series, DP3T, right angle
